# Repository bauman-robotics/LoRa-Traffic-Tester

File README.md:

# LoRa-Traffic-Tester

Проект для тестирования нагрузки  LoRa сети на базе ESP32-C3 Supermini и радиомодема E22-900M22S (SX1262).

Монитор загрузки сети Meshtastic без MQTT. 
Приемные ноды с Wi-Fi подключением слушают указанный LoRa-канал (предустановка 'Long Fast' по умолчанию). 
При обнаружении meshtastic пакетов, отправляют на удаленный сервер:
- уровень сигнала,
- длину пакета,
- заголовок пакета (ID ноды назначения и отправителя).

Ноды могут находиться в любой локации, необходимо обеспечить подключение к интернету через WiFi.
Онлайн визуальная статистика доступна с любого устройства через браузер и Grafana дашборды.
Количество нод ограничено количеством одновременных запросов к серверной базе данных (100).

## Описание

* Три идентичных LoRa-приемника с разными типами антенн работают в режиме Long Fast. Параллельный анализ RSSI от ближайших нод позволяет определить оптимальное расположение и тип антенны для максимальной чувствительности. 

* Окно графического интерфейса, конфигурация LoRa

* Окно графического интерфейса, конфигурация WiFi подключения. 

* Статистика и рейтиг наиболее использованных нод (отправители и получатели) за выбранный период времени. 

* Веб-интерфейс для просмотра информации, хранящейся в базе данных

* Организация бесперебойного питания на базе Bq25606*

Этот проект реализует LoRa трансивер для беспроводной связи на базе ESP32-C3 и модуля SX1262. Поддерживает передачу и прием данных через Serial интерфейс, управление через команды, сохранение данных во flash память.

Проект основан на [mini_lora_transceiver](https://github.com/lukuky64/mini_lora_transceiver/) с добавлением графического интерфейса для управления, серверной части.

## Серверная часть

Серверная часть проекта включает REST API на базе Flask для обработки данных LoRa сети. API принимает данные от нод ESP32, сохраняет их в базе данных PostgreSQL и предоставляет интерфейс для просмотра и анализа статистики.

- **API сервер**: Принимает POST запросы с данными о пакетах LoRa (уровень сигнала, ID ноды, длина пакета и т.д.)
- **База данных**: PostgreSQL с таблицей для хранения пакетов и метаданных, поддерживает одновременные подключения (до 100 по умолчанию)
- **Веб-интерфейс**: HTML представление данных для просмотра в браузере
- **Визуализация**: Интеграция с Grafana для создания дашбордов и графиков статистики сети
- **Эндпоинты**: Получение данных, добавление новых записей, очистка таблицы, проверка здоровья

Подробная информацию и инструкции по настройке находятся в папке [server_backend/](server_backend/).

## Структура проекта

```
LoRa-Traffic-Tester/
├── README.md                    # Этот файл
├── firmware/                    # Firmware для ESP32
│   ├── platformio.ini           # Конфигурация PlatformIO
│   ├── config.json              # Конфигурация Python скриптов сборки
│   ├── requirements.txt         # Зависимости Python
│   ├── build_script.py          # Скрипт сборки ESP32
│   ├── upload_script.py          # Скрипт загрузки на ESP32
│   ├── clean_script.py          # Скрипт очистки
│   ├── .gitignore               # Игнорируемые файлы Git
│   ├── src/
│   │   └── main.cpp             # Основной файл ESP32
│   ├── lib/
│   │   ├── lora_config.hpp      # Конфигурация LoRa и GPIO
│   │   ├── commander/           # Модуль команд
│   │   │   ├── commander.hpp
│   │   │   └── commander.cpp
│   │   ├── control/             # Основной контроллер
│   │   │   ├── control.hpp
│   │   │   └── control.cpp
│   │   ├── LoRaCom/             # LoRa коммуникации
│   │   │   ├── LoRaCom.hpp
│   │   │   └── LoRaCom.cpp
│   │   ├── SerialCom/           # Serial коммуникации
│   │   │   ├── SerialCom.hpp
│   │   │   └── SerialCom.cpp
│   │   ├── fileSystem/          # Работа с flash памятью
│   │   │   ├── saveFlash.hpp
│   │   │   └── saveFlash.cpp
│   │   ├── wifi_manager/        # WiFi управление
│   │   │   ├── wifi_manager.hpp
│   │   │   └── wifi_manager.cpp
│   │   └── fake_network_definitions.h # Заглушка сетевых определений
│   ├── bin/                     # Скомпилированные бинарники ESP32
│   ├── mesh_src/                # Исходники для mesh функционала
│   ├── Test_WiFi/               # Тестовая конфигурация с WiFi
│   │   ├── src/
│   │   ├── lib/
│   │   ├── bin/
│   │   ├── platformio.ini
│   │   ├── README.md
│   │   ├── requirements.txt
│   │   └── scripts/
│   ├── upload_mesh/             # Инструменты для загрузки mesh
│   │   ├── README.md
│   │   ├── requirements.txt
│   │   ├── flash.py
│   │   └── mesh_bin/
│   └── LoRa-Traffic-Tester.code-workspace # Настройки рабочего пространства VS Code
├── gui/                         # Графический интерфейс для управления
│   ├── gui.py                   # GUI для управления проектом
│   └── gui_config.json          # Конфигурация GUI
├── server_backend/              # Серверная часть проекта
│   └── lora_flask_api/
│       ├── lora_api.py          # REST API сервер на Flask
│       ├── config.py            # Конфигурация базы данных PostgreSQL
│       ├── How_to_create_DB_Postgress.md # Инструкция по настройке БД
│       └── Grafana/
│           ├── README.md
│           └── Grafana__dashboard_pro_v1.json
├── kicad/                       # KiCad PCB design files
│   ├── README.md
│   ├── .gitignore
│   ├── Info/                    # Documentation and datasheets
│   │   ├── E22_900M22s_info/
│   │   │   ├── E22-900M22s_info.c
│   │   │   ├── E22-900M22S_UserManual_EN_v1.3.pdf
│   │   │   └── E22-900M22s_pics/
│   │   ├── Esp32c3_supermini_info/
│   │   └── Signal_analyze/
│   └── Kicad_LoRa_v3_esp32c3_module_bq25606/  # Main PCB project
│       ├── ESP32C3-E22-Mesh-Node_v3.kicad_pcb
│       ├── ESP32C3-E22-Mesh-Node_v3.kicad_sch
│       ├── ESP32C3-E22-Mesh-Node_v3.kicad_pro
│       ├── ESP32C3-E22-Mesh-Node_v3.kicad_prl
│       ├── fp-info-cache
│       ├── fp-lib-table
│       ├── sym-lib-table
│       ├── footprints/
│       │   ├── Lora_Library.pretty/
│       │   └── VIP_metr_Library.pretty/
│       ├── symbols/
│       │   ├── Lora_lib.kicad_sym
│       │   └── VIP_metr_lib.kicad_sym
│       └── pics/
└── pics/                        # Изображения и скриншоты проекта
```

## Конфигурация GPIO

GPIO пины определены в `lib/lora_config.hpp`:

### Текущая конфигурация:
- **BUTTON_PIN**: GPIO9 (BOOT button)
- **LORA_RESET**: GPIO5 (RST от SX1262)
- **LORA_DIO1**: GPIO3 (DIO1 от SX1262)
- **LORA_RXEN**: GPIO2 (RX enable)
- **LORA_BUSY**: GPIO4 (BUSY от SX1262)
- **LORA_SCK**: GPIO10 (SPI clock)
- **LORA_MISO**: GPIO6 (SPI MISO)
- **LORA_MOSI**: GPIO7 (SPI MOSI)
- **LORA_CS**: GPIO8 (SPI CS)
- **INDICATOR_LED1**: GPIO2 (LED индикатор)

## Установка и настройка

### Требования
- Python 3.8+
- PlatformIO CLI
- Виртуальное окружение Python (venv)

### Настройка
1. Клонируйте репозиторий
2. Создайте виртуальное окружение в текущей папке: `python3 -m venv venv`
3. Активируйте виртуальное окружение: `source venv/bin/activate`
4. Установите зависимости: `pip install -r requirements.txt`
5. Настройте GPIO пины в `lib/lora_config.hpp` (если необходимо)
6. Настройте пути в `config.json` под вашу систему

### Конфигурационный файл config.json
```json
{
  "_guide": "Этот файл содержит конфигурацию для Python скриптов сборки/загрузки. Используется только venv_activate для автоматической активации виртуального окружения.",
  "venv_activate": "venv/bin/activate"
}
```

## Сборка и загрузка

### Сборка
```bash
python3 build_script.py
```
Собирает проект и копирует бинарные файлы в папку `bin/`.

### Загрузка
```bash
# Только загрузка существующего бинарника
python3 upload_script.py

# Сборка + загрузка
python3 upload_script.py --build
```

### Очистка
```bash
python3 clean_script.py
```
Удаляет папки `.pio`, `bin`.

## Использование

### Serial команды
Подключитесь к ESP32 через Serial (115200 baud) и используйте команды:

- `help` - список команд
- `command update gain <value>` - установить усиление
- `command update freqMhz <value>` - установить частоту
- `command update sf <value>` - установить spreading factor
- `command update bwKHz <value>` - установить bandwidth
- `command set status <0|1>` - включить/выключить автоматическую отправку статуса
- `data <payload>` - отправить данные
- `flash` - прочитать сохраненные данные из flash

### GUI
Запустите графический интерфейс:
```bash
python3 gui.py
```

## Особенности

- Автоматическая активация venv среды
- Сохранение данных во flash память
- Поддержка команд через Serial
- LED индикация состояния
- Настраиваемые параметры LoRa
- **Управление WiFi подключением:**
  - Конфигурирование настроек WiFi сети через графический интерфейс с сохранением во flash память
  - Возможность привязывания устройства к новой WiFi сети без перекомпиляции проекта
  - Детальное сканирование сетей с отображением канала и типа шифрования
  - Поддержка различных типов аутентификации (WPA2, WPA3, Open, etc.)
  - Диагностика подключения с подробными логами

## Разработка

Проект использует:
- **ESP32-C3** микроконтроллер
- **SX1262** LoRa модуль
- **RadioLib** библиотека для LoRa
- **PlatformIO** для сборки
- **ESP-IDF** framework

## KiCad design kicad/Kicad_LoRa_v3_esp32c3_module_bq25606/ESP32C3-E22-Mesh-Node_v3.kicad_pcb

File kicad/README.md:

# ESP32-C3 Super Mini E22-900M22S LoRa Mesh Gateway (SPI Version)

Проект Mesh-шлюза на базе компактной ESP32-C3 Super Mini и LoRa-модуля E22-900M22S с SPI интерфейсом для создания распределенных сетей с передачей данных через MQTT.

## 📋 Оглавление

- [Особенности](#особенности)
- [Схема подключения SPI](#схема-подключения-spi)
- [Распиновка ESP32-C3 Super Mini](#распиновка-esp32-c3-super-mini)
- [Установка и настройка](#установка-и-настройка)
- [Конфигурация SPI](#конфигурация-spi)
- [Использование](#использование)
- [Структура проекта](#структура-проекта)
- [Примеры кода](#примеры-кода)
- [Вклад в проект](#вклад-в-проект)
- [Лицензия](#лицензия)

## ✨ Особенности

- **ESP32-C3 Super Mini**: Ультракомпактная плата с RISC-V процессором
- **SPI интерфейс**: Программный SPI на свободных пинах
- **Mesh-топология**: Самоорганизующаяся сеть с автоматической маршрутизацией
- **Дальнобойность**: Работа в диапазоне 900 МГц с дальностью до 3 км
- **WiFi + BLE**: Дополнительные беспровятные интерфейсы
- **Миниатюрный размер**: Идеально для компактных устройств

// Serial for debugging
#define SERIAL_BAUD 115200

## ⚙️ Установка и настройка

### Требования

- **Аппаратные**:
  - ESP32-C3 Super Mini
  - E22-900M22S модуль
  - Антенна 900 МГц
  - Макетная плата или PCB

- **Программные**:
  - PlatformIO IDE или Arduino IDE
  - ESP32 Arduino Core 2.0.0+
  - Библиотека `RadioLib`

## 🔧 Программирование ESP32-C3 Super Mini

ESP32-C3 Super Mini имеет встроенный USB-to-Serial преобразователь на чипе CH343P или аналогичном, поэтому **программирование осуществляется напрямую через USB-C кабель**.

### Подключение для программирования:

1. **Просто подключите USB-C кабель** от компьютера к ESP32-C3 Super Mini
2. **Дополнительные соединения не требуются** - все необходимое уже на плате
3. **Автоматический сброс и загрузка** обеспечивается встроенной схемой

### Порядок программирования:

1. Подключите USB-C кабель к компьютеру и плате
2. В PlatformIO или Arduino IDE выберите правильный COM-порт
3. Для перехода в режим загрузки:
   - **Автоматически**: При начале загрузки через IDE
   - **Вручную**: Нажмите кнопку **BOOT** (если есть) и удерживая ее, нажмите **EN** (Reset), затем отпустите EN и потом BOOT

### Важные нюансы:

- **Драйверы**: На Windows может потребоваться установка драйверов для CH343P
- **Питание**: USB обеспечивает достаточное питание для программирования и работы
- **Кнопки**: На некоторых версиях платы есть кнопки BOOT и RESET для ручного управления

### Проверка подключения:

```cpp
void setup() {
  Serial.begin(115200);
  delay(1000);
  Serial.println("ESP32-C3 Super Mini started successfully!");
  Serial.printf("Chip ID: %08X\n", ESP.getEfuseMac());
  Serial.printf("Free Heap: %d bytes\n", ESP.getFreeHeap());
}

void loop() {
  Serial.println("Hello from ESP32-C3 Super Mini!");
  delay(1000);
}

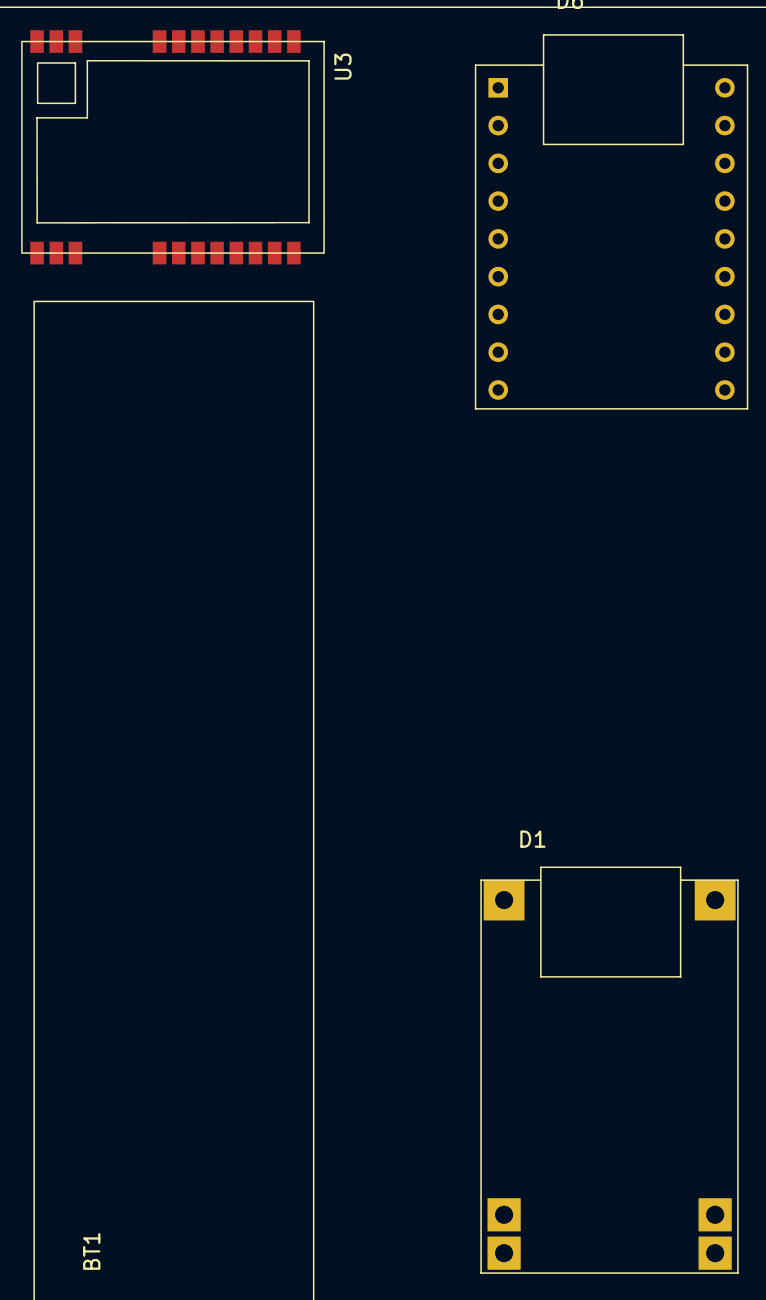
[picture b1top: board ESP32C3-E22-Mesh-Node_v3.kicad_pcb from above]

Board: 2 copper layers, 4 parts (0 on the bottom side), 10 nets, no tracks yet.

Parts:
BT1: Battery_Cell; 18650
D1: BQ25606
D6: ESP32_c6_zero
U3: E22-900M22s

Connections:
+3.3V: D6.14 (3.3V), U3.9 (VCC)
BUSY: D6.13 (GP4), U3.14 (BUSY)
CS: D6.4 (GP8), U3.19 (NSS)
DIO1: D6.12 (GP3), U3.13 (DIO1)
GND: D1.1 (-V), D1.3 (U-), D6.15 (GND), U3.1 (GND), U3.2 (GND), U3.3 (GND), U3.4 (GND), U3.5 (GND), U3.10 (GND), U3.11 (GND), U3.12 (GND), U3.20 (GND), U3.22 (GND)
MISO: D6.2 (GP6), U3.16 (MISO)
MOSI: D6.3 (GP7), U3.17 (MOSI)
unnamed: U3.7 (TX_EN), U3.8 (DIO2)
RST: D6.1 (GP5), U3.15 (NRST)
SCK: D6.6 (GP10), U3.18 (SCK)

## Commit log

2025-11-20 create
2025-11-20 info
2025-11-20 add server backend
2025-11-20 add info
2025-11-20 Реализация выбора режима приема (DUTY_CYCLE_RECEPTION)"
2025-11-21 Update documentation with latest changes
2025-11-21 Add final section 29 with duty cycle preamble correction instructions
2025-11-21 fix длина преамбулы 20 чирпов
2025-11-22 Извлечение ID отправителя из LoRa пакетов и использование в alarm_time
2025-11-22 Packet len looks like good
2025-11-23 Flask
2025-11-23 right dest id
2025-11-25 fix sender id
2025-11-25 decode description info
2025-11-25 add backend info, rm android and docker
2025-11-25 add backend info
2025-11-25 add info flash mesh
2025-11-25 rm upload_mesh.py
2025-11-27 add kicad
2025-11-27 fix project structure
2025-11-27 add bq25606 инфо
2025-11-27 fix инфо
2025-11-27 fix info
2025-11-27 Store WiFi Settings
2025-11-27 fix pics
2025-11-27 fix readme
2025-11-28 add https support for post
2025-11-28 ssl v1
2025-11-28 ssl v1 work
2025-11-29 queue
2025-11-29 batch fix
2025-12-01 fix Test_Wifi
2025-12-01 Test wifi minimum work
2025-12-01 Test Wifi minimal fully work
2025-12-01 Test Wifi увеличил таймаут.
2025-12-01 Half_work_sleep
2025-12-02 Первый пост запрос проходит на сервер с 10 попытки. Потом идут подряд. В чем дело, пока не разобрался.
2025-12-02 fix server timeouts Nginx
2025-12-03 fix nginx info
2025-12-05 fix info. Add http and https
2025-12-05 fix test wifi
2025-12-16 not correctly work
2025-12-16 config
2025-12-16 work version _ need to be dixconnected with pc

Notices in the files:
kicad/README.md:
License: MIT
